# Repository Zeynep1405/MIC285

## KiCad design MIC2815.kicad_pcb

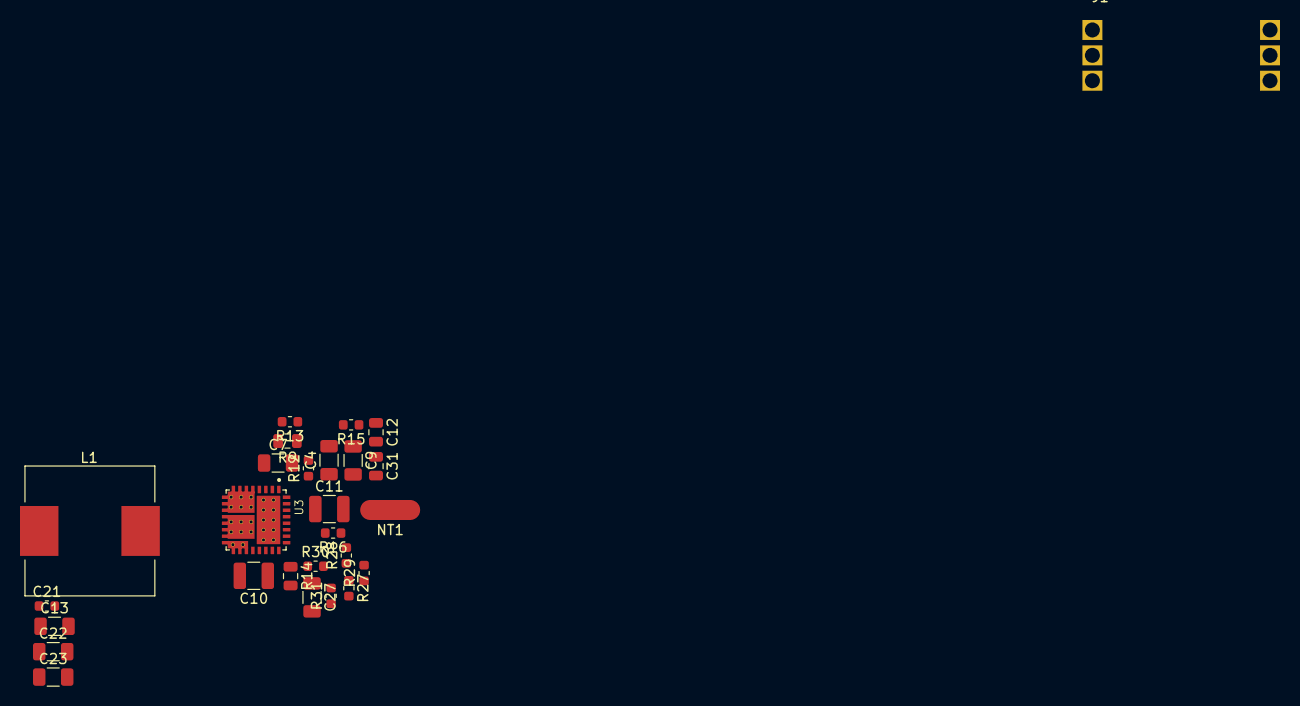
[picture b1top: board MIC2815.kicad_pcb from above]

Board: 2 copper layers, 27 parts (0 on the bottom side), 14 nets, no tracks yet.

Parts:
C4, C27: 1uF_100v; C_1206_3216Metric
C7, C9: 100nF_100v; C_1206_3216Metric
C10, C11: 4.7uF_25v; C_1210_3225Metric
C12: 4.7nF; C_0805_2012Metric
C13, C22, C23: 47uF; C_1206_3216Metric
C21: 100nF_100v; C_0603_1608Metric
C31: d.n.p; C_0805_2012Metric
J1: Conn_02x03_Counter_Clockwise; 6p7Dummy
L1: 8.2uH; L_Wuerth_HCI-1335
NT1: Net-Tie_2; NetTie-2_SMD_Pad2.0mm
R9, R14: 2.2R; R_0805_2012Metric
R12: 1.5k; R_0603_1608Metric
R13: 16.2k; R_0603_1608Metric
R15: 10k; R_0603_1608Metric
R16: 1.3k; R_0603_1608Metric
R27, R28, R29, R31: 100k; R_0603_1608Metric
R30: 0R; R_0603_1608Metric
U3: MIC28515; PHA

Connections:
+5V: C12.1, C13.1, C21.1, C22.1, C23.1, L1.1, R15.2, R30.2
/Sheet5FD8758D/EXTVDD: C27.1, R30.1, U3.23
/Sheet5FD8758D/FB: C9.2, C12.2, C31.1, R15.1, R16.2, U3.27
/Sheet5FD8758D/ILIM: R12.1, U3.1
/Sheet5FD8758D/PGND: C4.2, C10.2, NT1.1, U3.2, U3.16, U3.17, U3.18, U3.19, U3.19.1, U3.19.2, U3.19.3, U3.22, U3.29, U3.33, U3.33.1, U3.33.2, U3.33.3, U3.33.4, U3.33.5, U3.33.6, U3.33.7, U3.33.8, U3.33.9, U3.33.10
/Sheet5FD8758D/SW: C7.2, L1.2, R12.2, R13.2, U3.3, U3.12, U3.13, U3.14, U3.15, U3.20, U3.35, U3.35.1, U3.35.2, U3.35.3, U3.35.4, U3.35.5, U3.35.6
GND: C11.2, C13.2, C21.2, C22.2, C23.2, C27.2, C31.2, NT1.2, R16.1, R28.2, R31.1, U3.28
unnamed: C4.1, R9.1, U3.31
unnamed: C7.1, U3.4
unnamed: C9.1, R13.1
unnamed: C10.1, R14.1, U3.21
unnamed: R27.1, R31.2, U3.24
unnamed: R28.1, R29.2, U3.25
VDD: C11.1, R9.2, R14.2, R27.2, R29.1, U3.5, U3.6, U3.7, U3.8, U3.9, U3.10, U3.11, U3.26, U3.30, U3.34, U3.34.1, U3.34.2, U3.34.3, U3.34.4, U3.34.5, U3.34.6
